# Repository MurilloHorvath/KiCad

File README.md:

Repositório com proprosito de anexar meus projetos utilizando o software KiCAD

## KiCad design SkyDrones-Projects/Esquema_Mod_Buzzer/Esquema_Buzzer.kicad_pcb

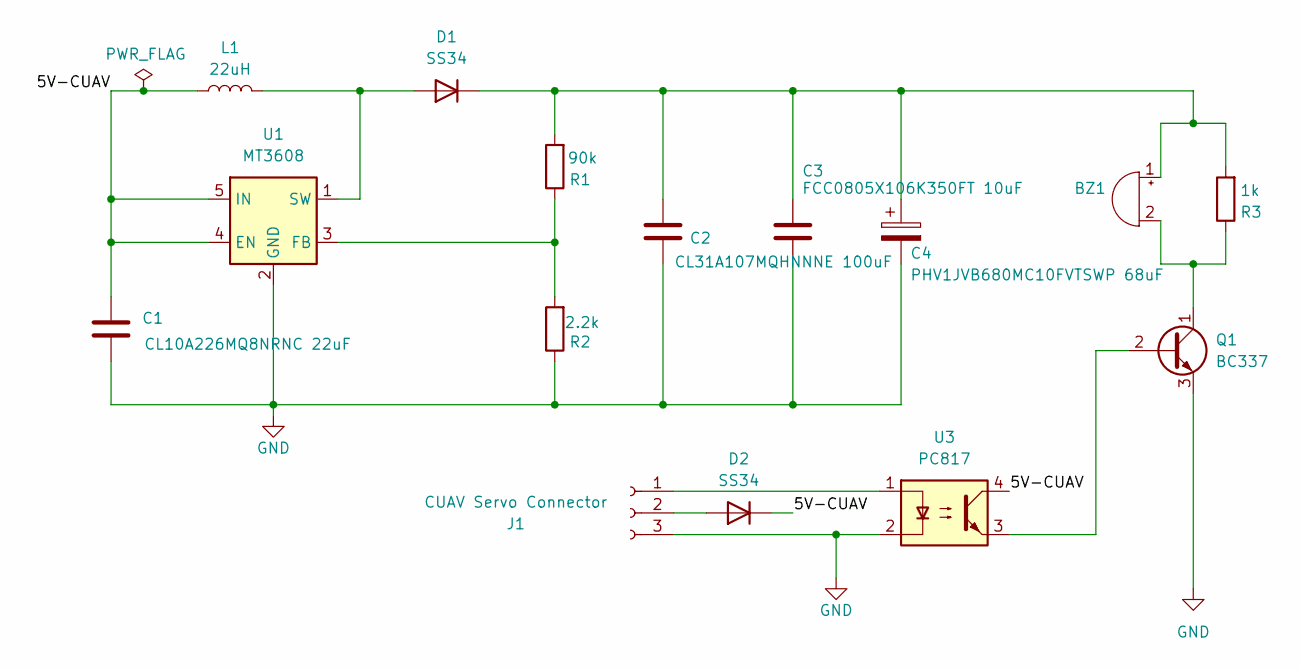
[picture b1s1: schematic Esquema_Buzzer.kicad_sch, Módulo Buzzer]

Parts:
BZ1: Buzzer; Buzzer_12x9.5RM7.6
C1: CL10A226MQ8NRNC 22uF; C_0603_1608Metric
C2: CL31A107MQHNNNE 100uF; C_1206_3216Metric
C3: FCC0805X106K350FT 10uF; C_0805_2012Metric
C4: PHV1JVB680MC10FVTSWP 68uF; CP_Elec_6.3x7.7
D1, D2: SS34; D_SMA
J1: CUAV Servo Connector; PinSocket_1x03_P2.00mm_Vertical
L1: 22uH; L_7.3x7.3_H4.5
Q1: BC337; SOT-223
R1: 90k; R_0201_0603Metric
R2: 2.2k; R_0201_0603Metric
R3: 1k; R_0402_1005Metric
U1: MT3608; SOT-23-6
U3: PC817; DIP-4_W7.62mm_SMDSocket_SmallPads

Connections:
/5V-CUAV: C1.1, D2.1 (K), L1.1, U1.4 (EN), U1.5 (IN), U3.4
GND: C1.2, C2.2, C3.2, C4.2, J1.3, Q1.3 (E), R2.1, U1.2 (GND), U3.2
unnamed: BZ1.1 (+), C2.1, C3.1, C4.1, D1.1 (K), R1.2, R3.2
unnamed: BZ1.2 (-), Q1.1 (C), R3.1
unnamed: D1.2 (A), L1.2, U1.1 (SW)
unnamed: D2.2 (A), J1.2
unnamed: J1.1, U3.1
unnamed: Q1.2 (B), U3.3
unnamed: R1.1, R2.2, U1.3 (FB)

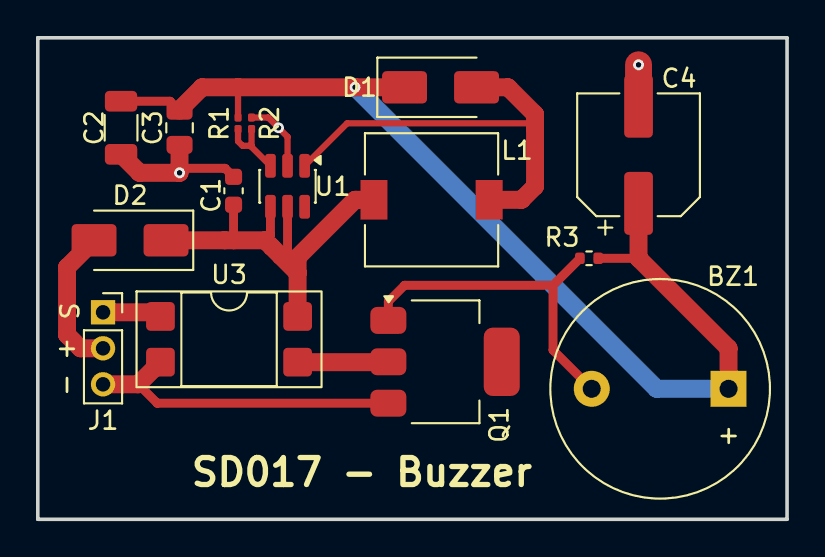
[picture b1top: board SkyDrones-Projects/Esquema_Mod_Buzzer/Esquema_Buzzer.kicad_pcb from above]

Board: 2 copper layers, 41.6 x 26.8 mm, 15 parts (0 on the bottom side), 9 nets.

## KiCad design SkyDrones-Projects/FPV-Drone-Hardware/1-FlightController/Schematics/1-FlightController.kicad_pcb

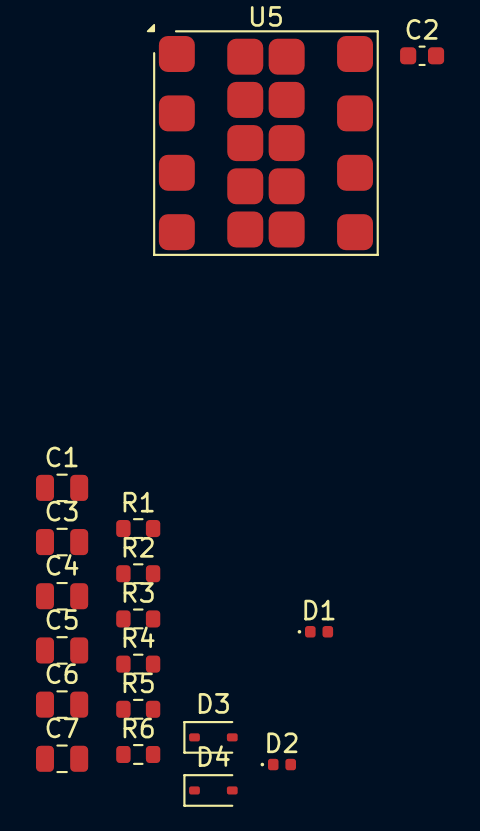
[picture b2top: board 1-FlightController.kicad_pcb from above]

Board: 2 copper layers, 18 parts (0 on the bottom side), 9 nets, no tracks yet.

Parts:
C1: 4.7uF; C_0805_2012Metric
C2: 100nF; C_0603_1608Metric
C3, C4, C5, C6, C7: 47uF; C_0805_2012Metric
D1, D2: 16-213/GHC-YR1S2/3T; LED_0402_1005Metric
D3, D4: 1N5819WS; D_SOD-323
R1: 10k; R_0603_1608Metric
R2: 75k; R_0603_1608Metric
R3: 14k3; R_0603_1608Metric
R4: 1k; R_0603_1608Metric
R5, R6: 100k; R_0603_1608Metric
U5: MPM3550EGLE; MPS_LGA-18-10EP_12x12mm_P3.3mm

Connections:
/5V: D3.1 (K), D4.1 (K)
/5VREG: C3.1, C4.1, C5.1, C6.1, C7.1, D2.2 (A), D4.2 (A), R2.1, U5.5 (VOUT)
/VBAT: C1.1, C2.1, D1.2 (A), R5.1, U5.8 (VIN)
GND: C1.2, C2.2, C3.2, C4.2, C5.2, C6.2, C7.2, R1.2, R3.2, R4.2, R6.1, U5.6 (GND), U5.7 (GND), U5.9 (GND), U5.10 (GND), U5.11 (GND), U5.12 (GND), U5.13 (GND), U5.14 (GND), U5.15 (GND), U5.16 (GND), U5.17 (GND), U5.18 (GND)
unnamed: D1.1 (K), R1.1
unnamed: D2.1 (K), R4.1
unnamed: R5.2, U5.1 (EN)
unnamed: R2.2, R3.1, U5.4 (FB)
unnamed: R6.2, U5.2 (RFREQ)

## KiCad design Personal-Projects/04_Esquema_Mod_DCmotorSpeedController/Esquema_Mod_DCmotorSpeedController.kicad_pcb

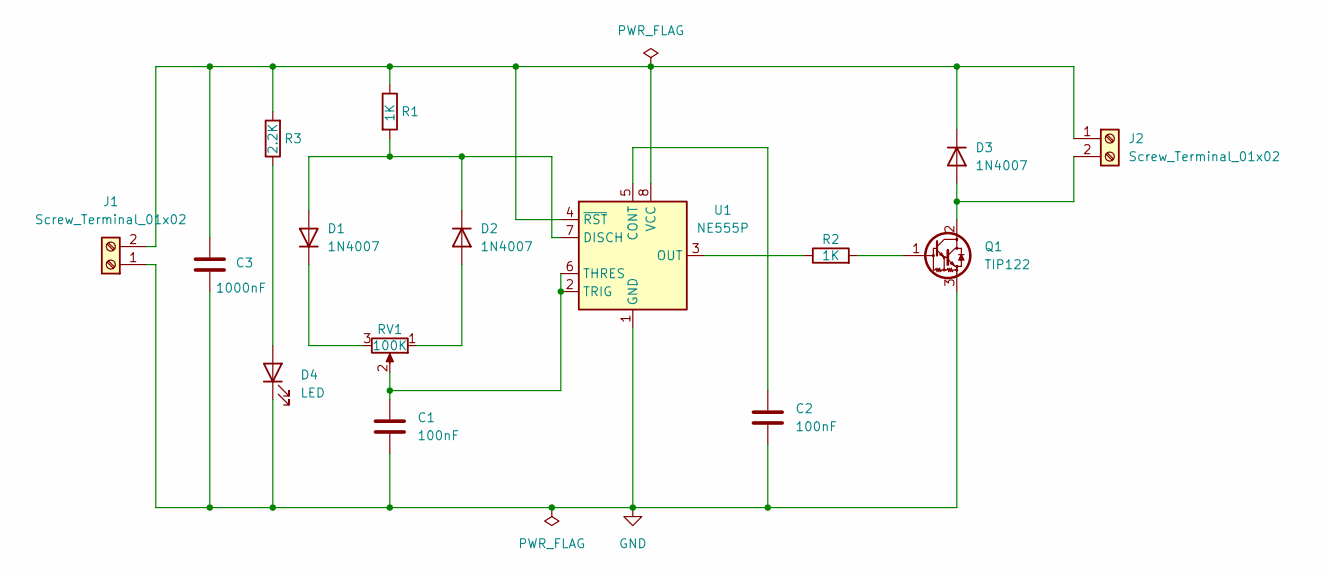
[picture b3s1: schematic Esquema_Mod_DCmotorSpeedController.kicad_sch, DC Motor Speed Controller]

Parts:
C1, C2: 100nF; C_Disc_D4.7mm_W2.5mm_P5.00mm
C3: 1000nF; CP_Radial_D10.0mm_P5.00mm
D1, D2, D3: 1N4007; D_DO-41_SOD81_P10.16mm_Horizontal
D4: LED; LED_D5.0mm
J1, J2: Screw_Terminal_01x02; TerminalBlock_MaiXu_MX126-5.0-02P_1x02_P5.00mm
Q1: TIP122; TO-220-3_Vertical
R1, R2: 1K; R_Axial_DIN0204_L3.6mm_D1.6mm_P7.62mm_Horizontal
R3: 2.2K; R_Axial_DIN0204_L3.6mm_D1.6mm_P7.62mm_Horizontal
RV1: 100K; Potentiometer_Alps_RK163_Single_Horizontal
U1: NE555P; DIP-8_W7.62mm

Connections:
GND: C1.2, C2.2, C3.2, D4.1 (K), J1.1, Q1.3 (E), U1.1 (GND)
unnamed: D1.2 (A), D2.1 (K), R1.2, U1.7 (DISCH)
unnamed: D1.1 (K), RV1.3
unnamed: D2.2 (A), RV1.1
unnamed: D3.2 (A), J2.2, Q1.2 (C)
unnamed: C3.1, D3.1 (K), J1.2, J2.1, R1.1, R3.2, U1.4 (~RST), U1.8 (VCC)
unnamed: D4.2 (A), R3.1
unnamed: Q1.1 (B), R2.2
unnamed: C2.1, U1.5 (CONT)
unnamed: R2.1, U1.3 (OUT)
unnamed: C1.1, RV1.2, U1.2 (TRIG), U1.6 (THRES)

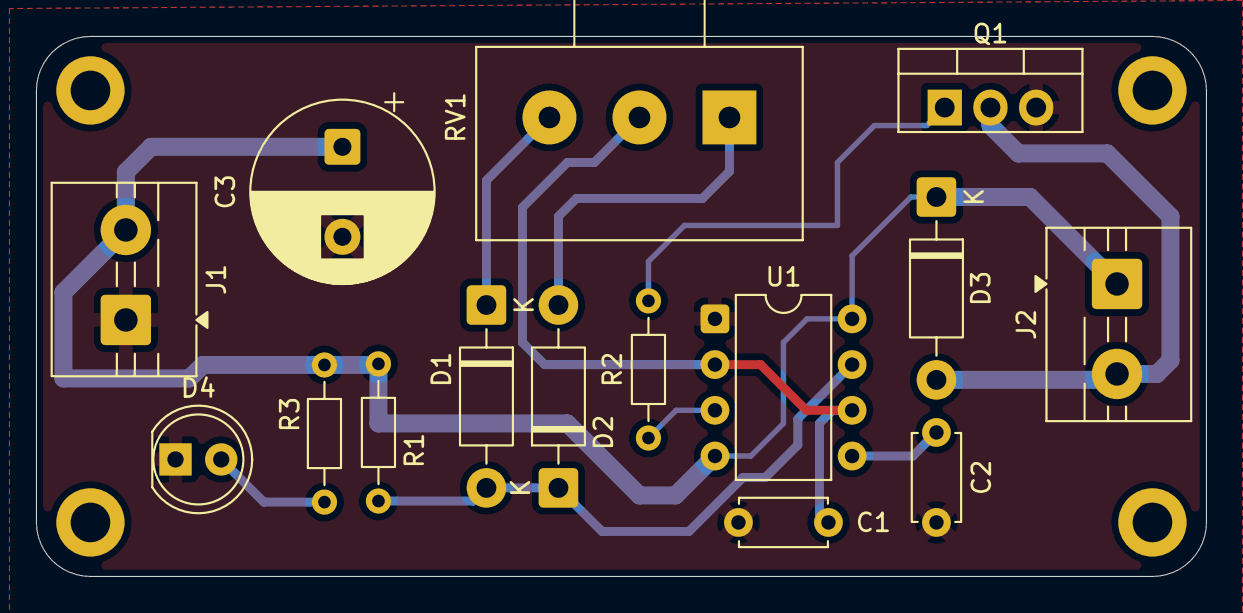
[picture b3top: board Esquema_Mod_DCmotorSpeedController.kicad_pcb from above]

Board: 2 copper layers, 65.0 x 30.0 mm, 15 parts (0 on the bottom side), 11 nets.

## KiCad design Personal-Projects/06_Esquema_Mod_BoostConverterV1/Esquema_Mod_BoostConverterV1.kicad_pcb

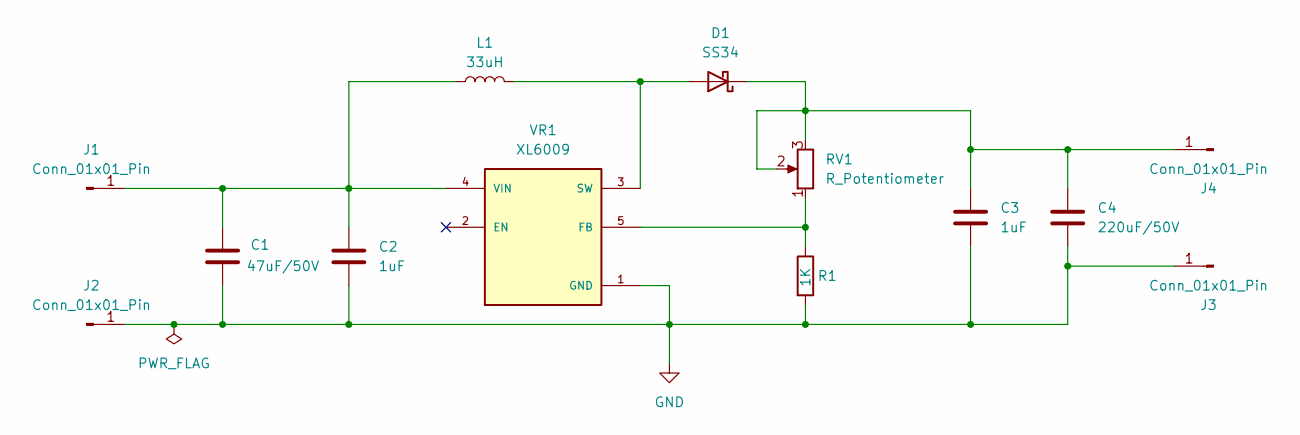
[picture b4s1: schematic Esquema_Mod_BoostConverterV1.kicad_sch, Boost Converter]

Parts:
C1: 47uF/50V; C_Radial_D6.3mm_H11.0mm_P2.50mm
C2, C3: 1uF; C_0805_2012Metric
C4: 220uF/50V; C_Radial_D6.3mm_H11.0mm_P2.50mm
D1: SS34; D_SMA
J1, J2, J3, J4: Conn_01x01_Pin; PinHeader_1x01_P2.54mm_Vertical
L1: 33uH; L_12x12mm_H8mm
R1: 1K; R_1206_3216Metric
RV1: R_Potentiometer; Potentiometer_Bourns_3296W_Vertical
VR1: XL6009; DPAK170P1435X465-6N; PARTREV 1.1

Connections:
GND: C1.2, C2.2, C3.2, C4.2, J2.1 (Pin_1_1), J3.1 (Pin_1_1), R1.2, VR1.1 (GND)
unnamed: D1.2 (A), L1.2, VR1.3 (SW), VR1.6 (SW)
unnamed: C3.1, C4.1, D1.1 (K), J4.1 (Pin_1_1), RV1.2, RV1.3
unnamed: C1.1, C2.1, J1.1 (Pin_1_1), L1.1, VR1.4 (VIN)
unnamed: R1.1, RV1.1, VR1.5 (FB)

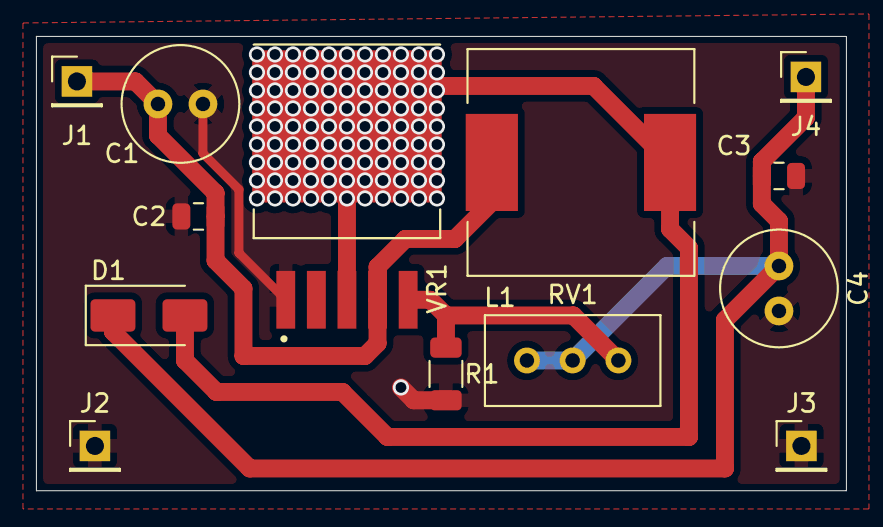
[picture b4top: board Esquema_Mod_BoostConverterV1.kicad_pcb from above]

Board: 2 copper layers, 45.0 x 25.2 mm, 13 parts (0 on the bottom side), 5 nets.

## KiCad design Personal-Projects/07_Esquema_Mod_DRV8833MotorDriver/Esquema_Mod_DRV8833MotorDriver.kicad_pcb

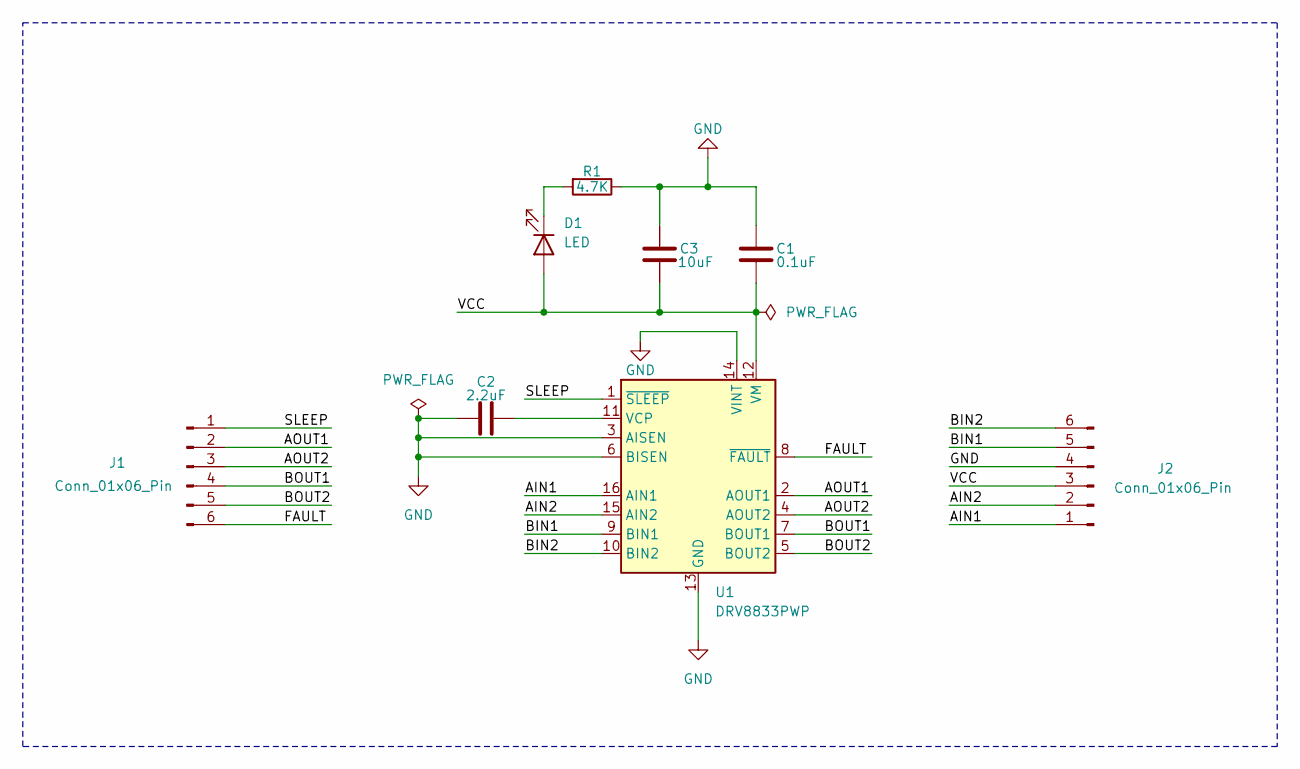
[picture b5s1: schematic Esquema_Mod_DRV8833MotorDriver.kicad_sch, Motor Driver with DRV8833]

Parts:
C1: 0.1uF; C_0805_2012Metric
C2: 2.2uF; C_0805_2012Metric
C3: 10uF; CP_EIA-6032-20_AVX-F
D1: LED; LED_0805_2012Metric
J1, J2: Conn_01x06_Pin; PinHeader_1x06_P2.54mm_Vertical
R1: 4.7K; R_0805_2012Metric
U1: DRV8833PWP; HTSSOP-16-1EP_4.4x5mm_P0.65mm_EP3.4x5mm_Mask2.46x2.31mm_The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

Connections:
/AIN1: J2.1, U1.16 (AIN1)
/AIN2: J2.2, U1.15 (AIN2)
/AOUT1: J1.2, U1.2 (AOUT1)
/AOUT2: J1.3, U1.4 (AOUT2)
/BIN1: J2.5, U1.9 (BIN1)
/BIN2: J2.6, U1.10 (BIN2)
/BOUT1: J1.4, U1.7 (BOUT1)
/BOUT2: J1.5, U1.5 (BOUT2)
/FAULT: J1.6, U1.8 (~FAULT)
/SLEEP: J1.1, U1.1 (~SLEEP)
/VCC: C1.2, C3.2, D1.2 (A), J2.3, U1.12 (VM)
GND: C1.1, C2.1, C3.1, J2.4, R1.1, U1.3 (AISEN), U1.6 (BISEN), U1.13 (GND), U1.14 (VINT), U1.17 (GND)
unnamed: D1.1 (K), R1.2
unnamed: C2.2, U1.11 (VCP)

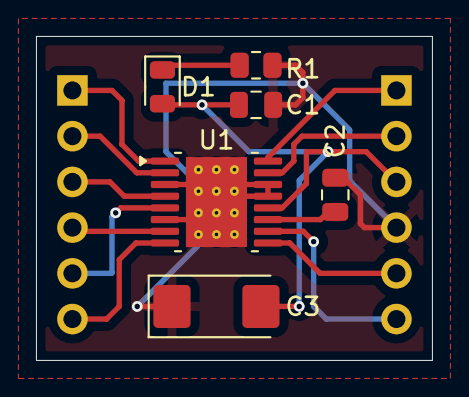
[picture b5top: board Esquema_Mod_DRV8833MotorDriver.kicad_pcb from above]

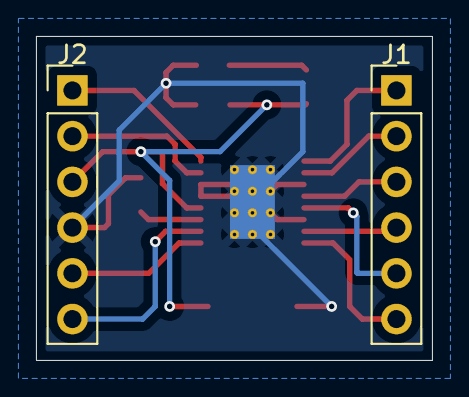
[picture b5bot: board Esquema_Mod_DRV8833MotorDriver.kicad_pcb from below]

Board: 2 copper layers, 22.0 x 18.0 mm, 8 parts (2 on the bottom side), 14 nets.

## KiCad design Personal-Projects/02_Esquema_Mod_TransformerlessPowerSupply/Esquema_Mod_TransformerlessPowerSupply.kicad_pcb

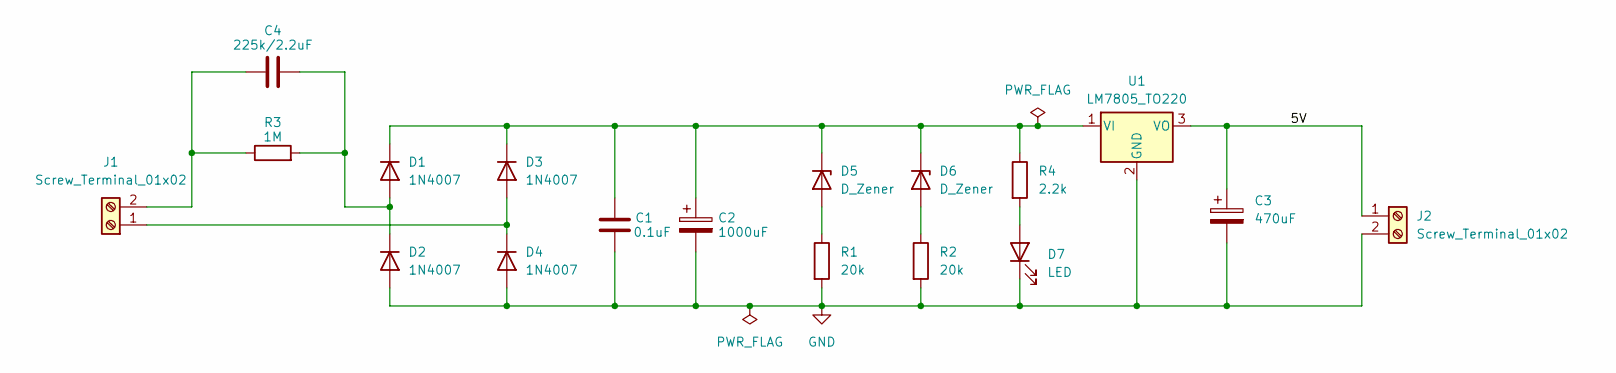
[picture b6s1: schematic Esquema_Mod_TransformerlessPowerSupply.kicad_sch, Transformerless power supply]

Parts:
C1: 0.1uF; C_Disc_D4.7mm_W2.5mm_P5.00mm
C2: 1000uF; CP_Radial_D10.0mm_P5.00mm
C3: 470uF; CP_Radial_D10.0mm_P3.80mm
C4: 225k/2.2uF; C_Rect_L18.0mm_W6.0mm_P15.00mm_FKS3_FKP3
D1, D2, D3, D4: 1N4007; D_DO-41_SOD81_P10.16mm_Horizontal
D5, D6: D_Zener; D_A-405_P7.62mm_Horizontal
D7: LED; LED_D5.0mm
J1, J2: Screw_Terminal_01x02; TerminalBlock_MaiXu_MX126-5.0-02P_1x02_P5.00mm
R1, R2: 20k; R_Axial_DIN0207_L6.3mm_D2.5mm_P7.62mm_Horizontal
R3: 1M; R_Axial_DIN0207_L6.3mm_D2.5mm_P7.62mm_Horizontal
R4: 2.2k; R_Axial_DIN0207_L6.3mm_D2.5mm_P7.62mm_Horizontal
U1: LM7805_TO220; TO-220-3_Vertical

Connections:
/5V: C3.1, J2.1, U1.3 (VO)
GND: C1.2, C2.2, C3.2, D2.2 (A), D4.2 (A), D7.1 (K), J2.2, R1.2, R2.2, U1.2 (GND)
unnamed: C4.2, D1.2 (A), D2.1 (K), R3.2
unnamed: C1.1, C2.1, D1.1 (K), D3.1 (K), D5.1 (K), D6.1 (K), R4.1, U1.1 (VI)
unnamed: D3.2 (A), D4.1 (K), J1.1
unnamed: D5.2 (A), R1.1
unnamed: D6.2 (A), R2.1
unnamed: D7.2 (A), R4.2
unnamed: C4.1, J1.2, R3.1

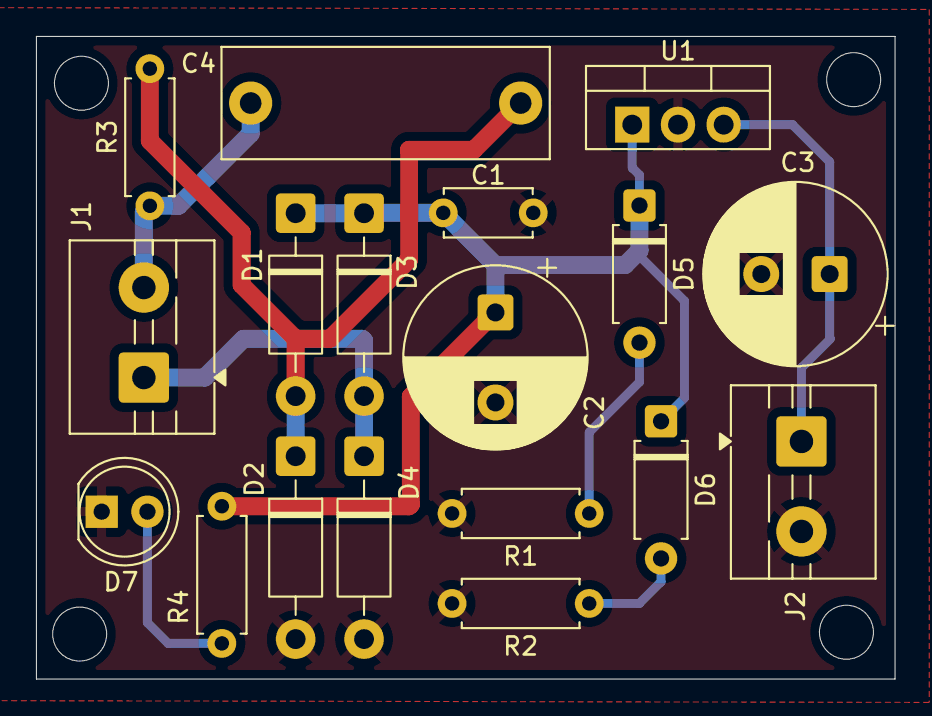
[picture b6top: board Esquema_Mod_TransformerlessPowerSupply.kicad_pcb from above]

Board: 2 copper layers, 47.7 x 35.7 mm, 18 parts (0 on the bottom side), 9 nets.

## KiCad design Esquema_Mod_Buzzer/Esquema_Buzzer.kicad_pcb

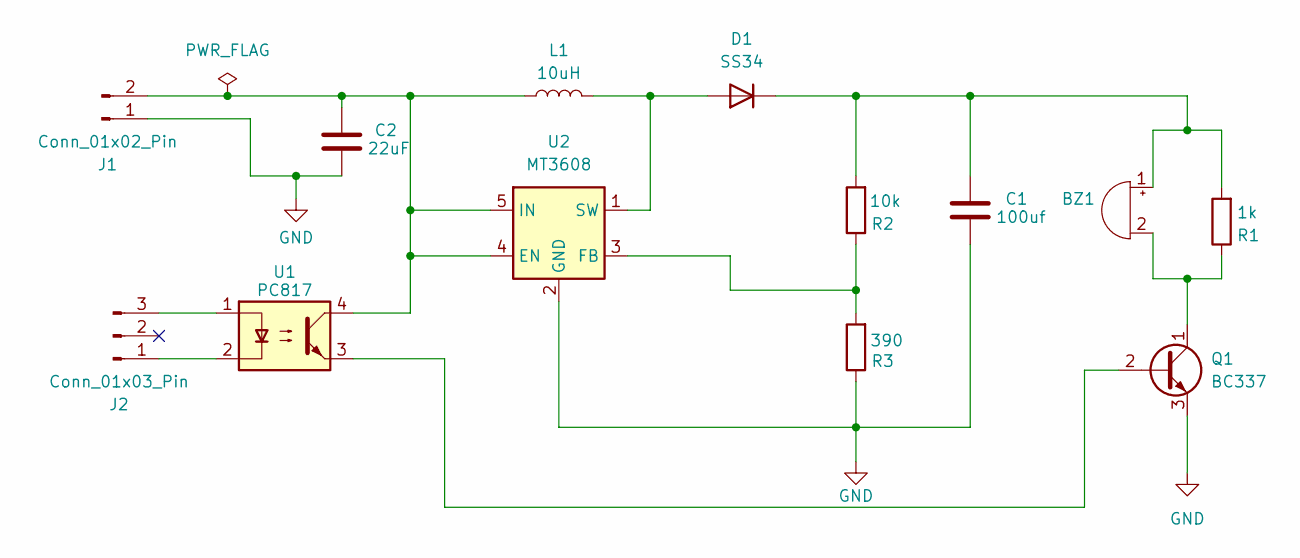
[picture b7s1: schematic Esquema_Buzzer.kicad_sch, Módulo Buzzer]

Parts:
BZ1: Buzzer; Buzzer_12x9.5RM7.6
C1: 100uf; CP_Elec_3x5.3
C2: 22uF; CP_Elec_3x5.3
D1: SS34; D_2114_3652Metric_Pad1.85x3.75mm_HandSolder
J1: Conn_01x02_Pin; AMASS_XT30PW-M_1x02_P2.50mm_Horizontal
J2: Conn_01x03_Pin; PinHeader_1x03_P1.00mm_Horizontal
L1: 10uH; L_7.3x7.3_H4.5
Q1: BC337; TO-92_Inline
R1: 1k; R_Axial_DIN0204_L3.6mm_D1.6mm_P5.08mm_Horizontal
R2: 10k; R_0201_0603Metric
R3: 390; R_0201_0603Metric
U1: PC817; DIP-4_W7.62mm
U2: MT3608; SOT-23-6

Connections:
GND: C1.2, C2.2, J1.1, Q1.3 (E), R3.1, U2.2 (GND)
unnamed: BZ1.1 (+), C1.1, D1.1 (K), R1.2, R2.2
unnamed: BZ1.2 (-), Q1.1 (C), R1.1
unnamed: D1.2 (A), L1.2, U2.1 (SW)
unnamed: C2.1, J1.2, L1.1, U1.4, U2.4 (EN), U2.5 (IN)
unnamed: J2.1, U1.2
unnamed: J2.3, U1.1
unnamed: Q1.2 (B), U1.3
unnamed: R2.1, R3.2, U2.3 (FB)

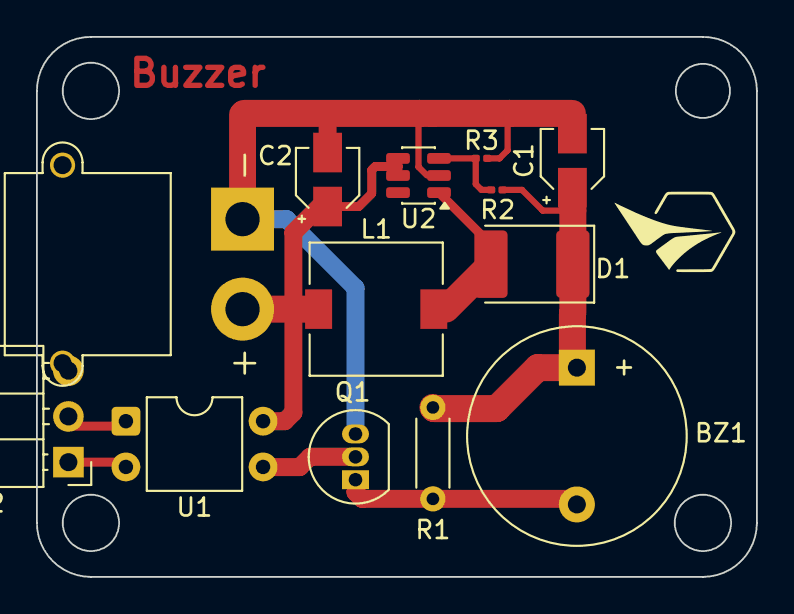
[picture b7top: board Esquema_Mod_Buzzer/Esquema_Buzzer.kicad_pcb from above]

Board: 2 copper layers, 40.0 x 30.0 mm, 13 parts (0 on the bottom side), 9 nets.

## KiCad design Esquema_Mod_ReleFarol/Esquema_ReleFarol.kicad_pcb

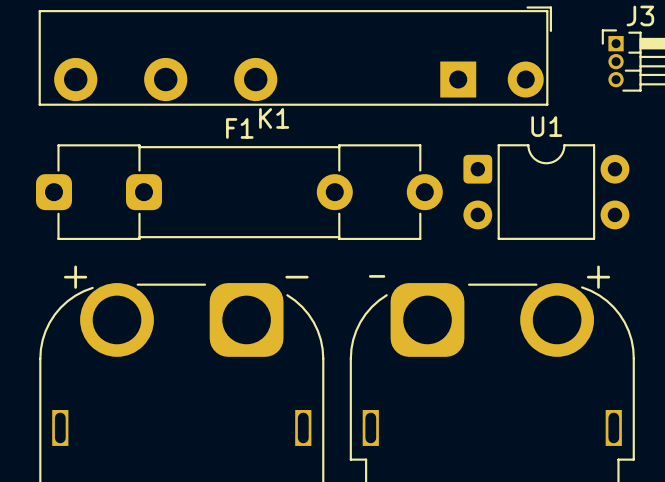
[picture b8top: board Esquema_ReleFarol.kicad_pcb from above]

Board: 2 copper layers, 6 parts (0 on the bottom side), 5 nets, no tracks yet.

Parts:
F1: F3A 250V; Fuseholder_Clip-5x20mm_Littelfuse_519_Inline_P20.60x5.00mm_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
J1: Conn_01x02_Socket; AMASS_XT60PW-F_1x02_P7.20mm_Horizontal
J2: Conn_01x02_Pin; AMASS_XT60PW-M_1x02_P7.20mm_Horizontal
J3: Servo CUAV A8; PinHeader_1x03_P1.00mm_Horizontal
K1: HF41F; Relay_SPDT_Finder_34.51_Vertical
U1: 817B; DIP-4_W7.62mm

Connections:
unnamed: J1.1, J2.1
unnamed: F1.2, J1.2
unnamed: J2.2, K1.12
unnamed: J3.1, U1.2, U1.3
unnamed: J3.3, U1.1

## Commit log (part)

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2026-02-20 [ADD]
2026-03-06 [ADD] some projects
2026-04-17 [UP] Upgrade Buzzer
2026-06-12 [UPDATE STRUCTURE]
2026-06-12 [ADD] project 09
